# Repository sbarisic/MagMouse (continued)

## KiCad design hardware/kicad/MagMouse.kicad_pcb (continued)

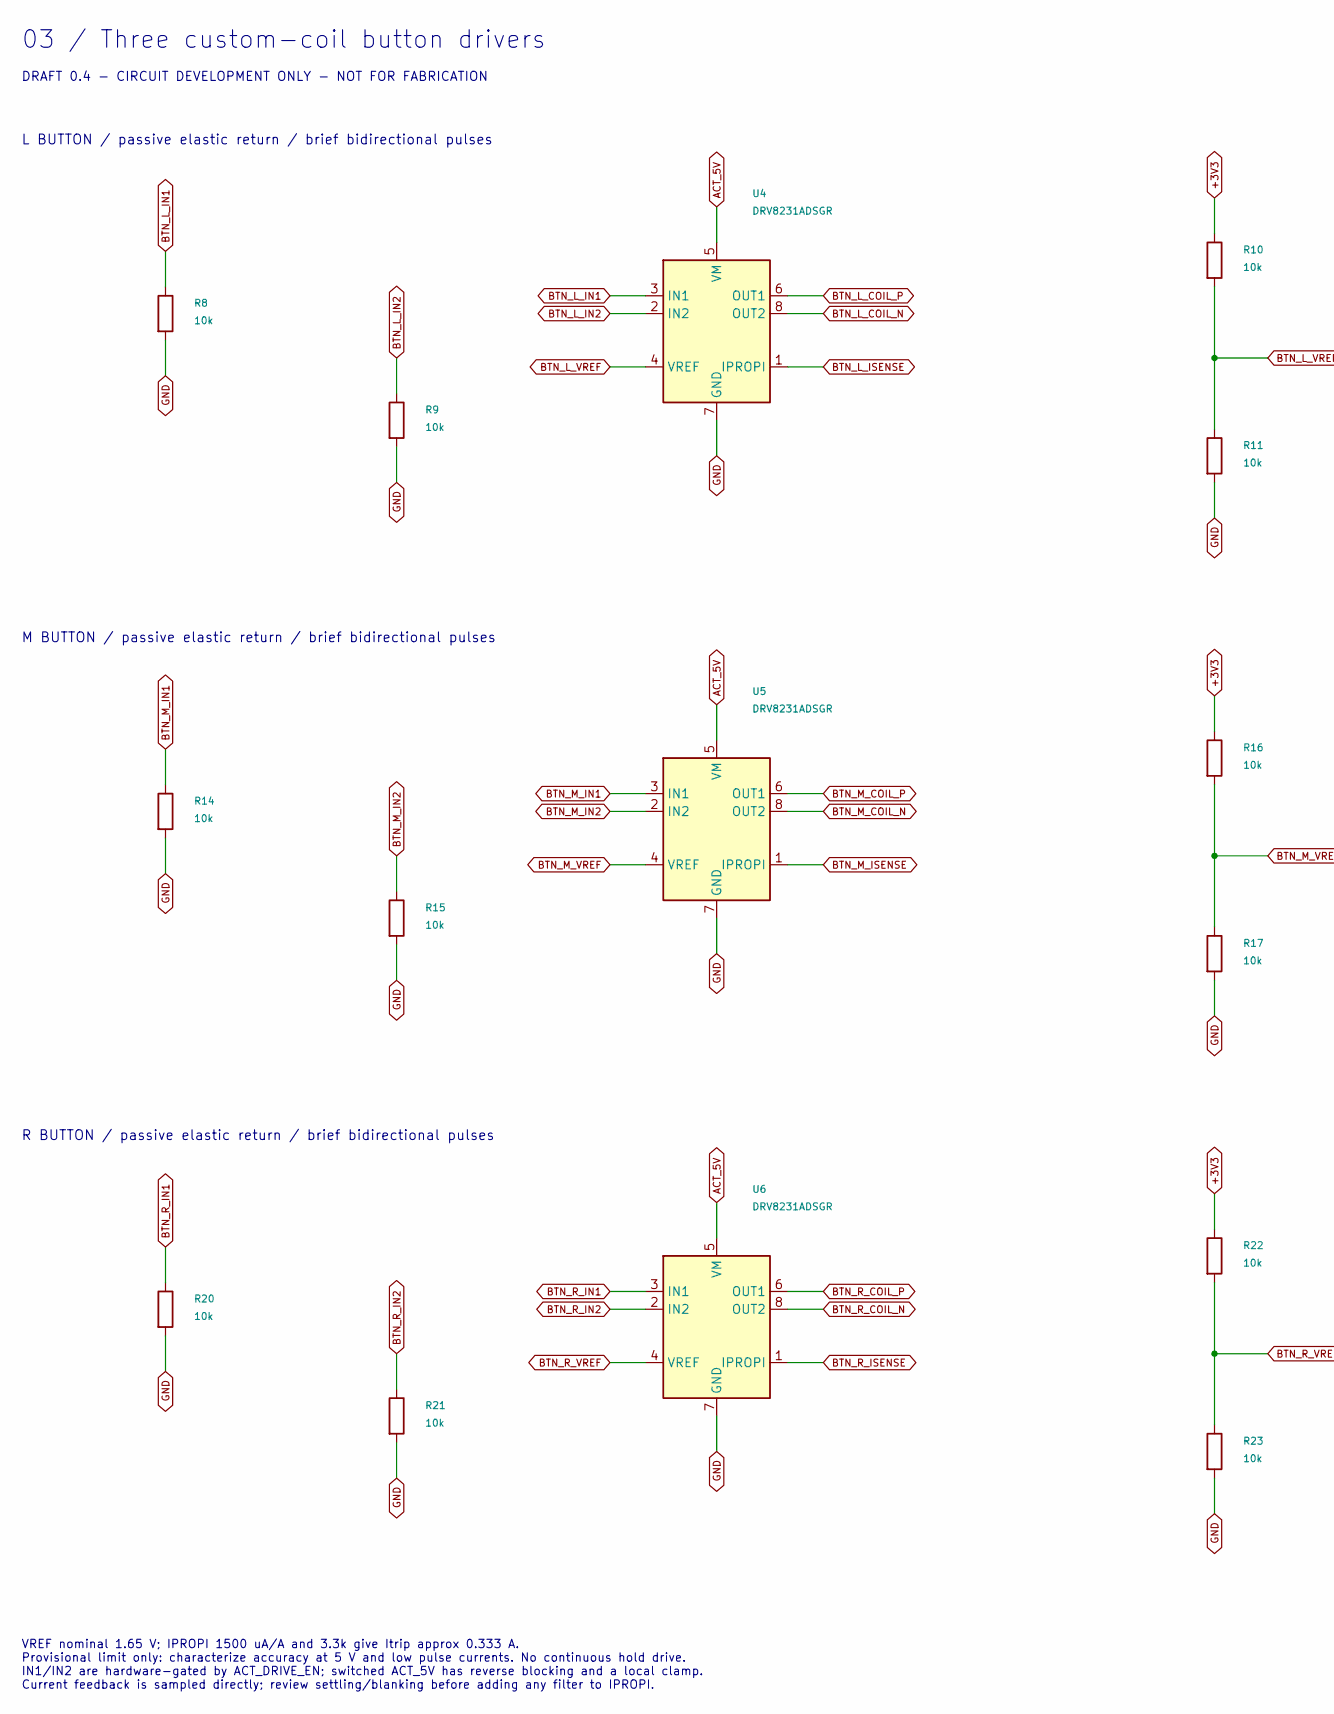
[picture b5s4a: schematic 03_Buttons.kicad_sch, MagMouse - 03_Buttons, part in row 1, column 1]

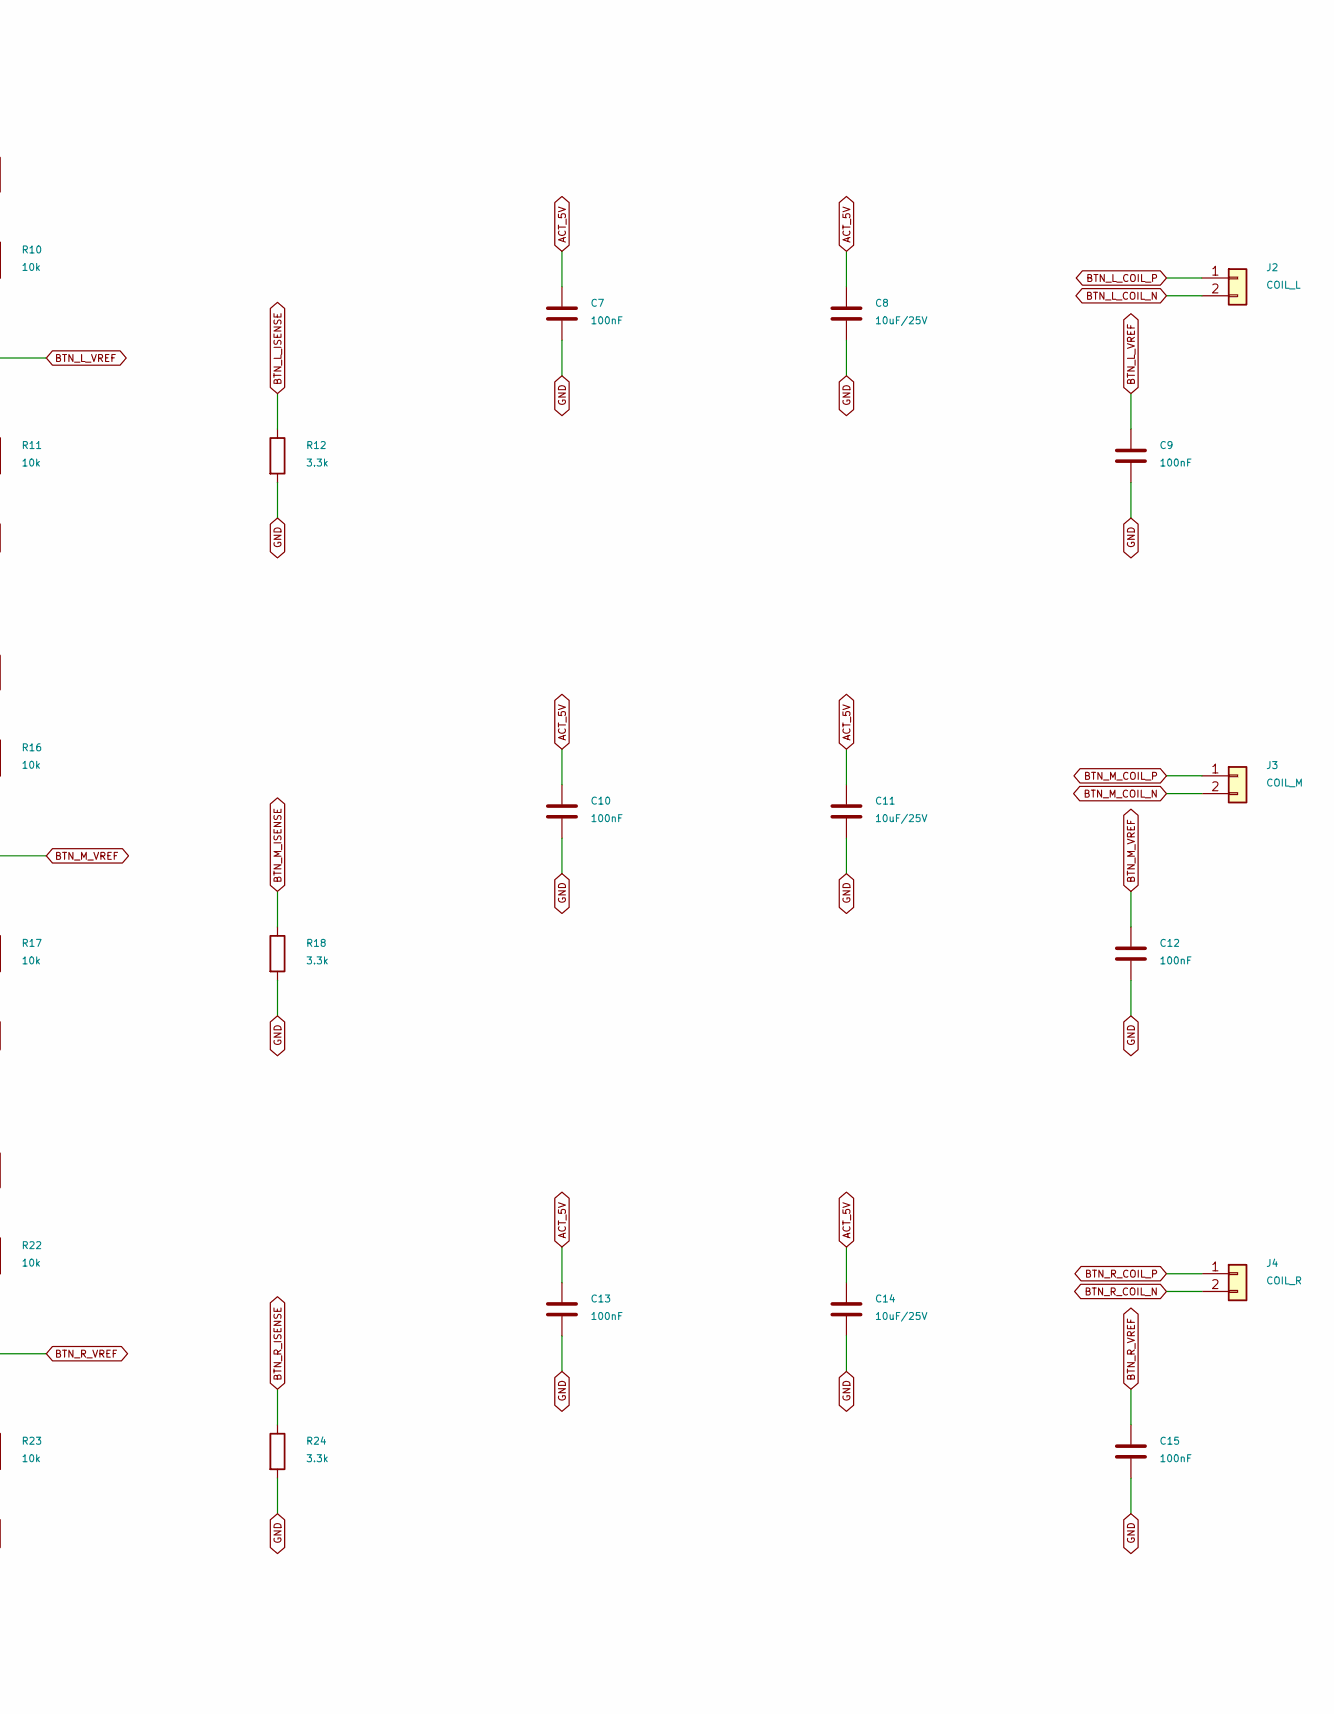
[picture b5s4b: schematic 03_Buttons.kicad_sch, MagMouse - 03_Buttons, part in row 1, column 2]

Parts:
C7, C9, C10, C12, C13, C15: 100nF; C_0603_1608Metric; MPN CC0603KRX7R9BB104; LCSC C14663
C8, C11, C14: 10uF/25V; C_0805_2012Metric; MPN CL21A106KAYNNNE; LCSC C15850
J2: COIL_L; JST_PH_B2B-PH-SM4-TB_1x02-1MP_P2.00mm_Vertical; MPN B2B-PH-SM4-TBT(LF)(SN); LCSC C265003
J3: COIL_M; JST_PH_B2B-PH-SM4-TB_1x02-1MP_P2.00mm_Vertical; MPN B2B-PH-SM4-TBT(LF)(SN); LCSC C265003
J4: COIL_R; JST_PH_B2B-PH-SM4-TB_1x02-1MP_P2.00mm_Vertical; MPN B2B-PH-SM4-TBT(LF)(SN); LCSC C265003
R8, R9, R10, R11, R14, R15, R16, R17, R20, R21, R22, R23: 10k; R_0603_1608Metric; MPN 0603WAF1002T5E; LCSC C25804
R12, R18, R24: 3.3k; R_0603_1608Metric; MPN 0603WAF3301T5E; LCSC C22978
U4, U5, U6: DRV8231ADSGR; Texas_DSG0008A_WSON-8-1EP_2x2mm_P0.5mm_EP0.9x1.6mm; MPN DRV8231ADSGR; LCSC C5139865

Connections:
+3V3: R10.1, R16.1, R22.1; also elsewhere on the board
ACT_5V: C7.1, C8.1, C10.1, C11.1, C13.1, C14.1, U4.5 (VM), U5.5 (VM), U6.5 (VM); also elsewhere on the board
BTN_L_COIL_N: J2.2, U4.8 (OUT2)
BTN_L_COIL_P: J2.1, U4.6 (OUT1)
BTN_L_IN1: R8.1, U4.3 (IN1); also elsewhere on the board
BTN_L_IN2: R9.1, U4.2 (IN2); also elsewhere on the board
BTN_L_ISENSE: R12.1, U4.1 (IPROPI); also elsewhere on the board
BTN_L_VREF: C9.1, R10.2, R11.1, U4.4 (VREF)
BTN_M_COIL_N: J3.2, U5.8 (OUT2)
BTN_M_COIL_P: J3.1, U5.6 (OUT1)
BTN_M_IN1: R14.1, U5.3 (IN1); also elsewhere on the board
BTN_M_IN2: R15.1, U5.2 (IN2); also elsewhere on the board
BTN_M_ISENSE: R18.1, U5.1 (IPROPI); also elsewhere on the board
BTN_M_VREF: C12.1, R16.2, R17.1, U5.4 (VREF)
BTN_R_COIL_N: J4.2, U6.8 (OUT2)
BTN_R_COIL_P: J4.1, U6.6 (OUT1)
BTN_R_IN1: R20.1, U6.3 (IN1); also elsewhere on the board
BTN_R_IN2: R21.1, U6.2 (IN2); also elsewhere on the board
BTN_R_ISENSE: R24.1, U6.1 (IPROPI); also elsewhere on the board
BTN_R_VREF: C15.1, R22.2, R23.1, U6.4 (VREF)
GND: C7.2, C8.2, C9.2, C10.2, C11.2, C12.2, C13.2, C14.2, C15.2, R8.2, R9.2, R11.2, R12.2, R14.2, R15.2, R17.2, R18.2, R20.2, R21.2, R23.2, R24.2, U4.7 (GND), U4.9 (GND), U5.7 (GND), U5.9 (GND), U6.7 (GND), U6.9 (GND); also elsewhere on the board

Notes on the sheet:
03 / Three custom-coil button drivers
DRAFT 0.4 - CIRCUIT DEVELOPMENT ONLY - NOT FOR FABRICATION
L BUTTON / passive elastic return / brief bidirectional pulses
M BUTTON / passive elastic return / brief bidirectional pulses
R BUTTON / passive elastic return / brief bidirectional pulses
VREF nominal 1.65 V; IPROPI 1500 uA/A and 3.3k give Itrip approx 0.333 A. Provisional limit only: characterize accuracy at 5 V and low pulse currents. No continuous hold drive. IN1/IN2 are hardware-gated by ACT_DRIVE_EN; switched ACT_5V has reverse blocking and a local clamp. Current feedback is sa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

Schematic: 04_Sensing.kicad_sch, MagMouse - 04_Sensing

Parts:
C16, C17, C18: 100nF; C_0603_1608Metric; MPN CC0603KRX7R9BB104; LCSC C14663
C19, C20, C21: 1uF/50V; C_0603_1608Metric; MPN CL10A105KB8NNNC; LCSC C15849
U7, U8, U9: TMAG5253BA2IQDMRR; Texas_X2SON-4-1EP_1.1x1.4mm_P0.5mm_EP0.8x0.6mm; MPN TMAG5253BA2IQDMRR; LCSC C35414983
U10: ADS7038IRTER; WQFN-16-1EP_3x3mm_P0.5mm_EP1.68x1.68mm; MPN ADS7038IRTER; LCSC C2871580

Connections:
+3V3: C16.1, C17.1, C18.1, C19.1, C20.1, U7.1 (VCC), U8.1 (VCC), U9.1 (VCC), U10.7 (AVDD), U10.10 (DVDD); also elsewhere on the board
ACT_VMON: U10.6 (AIN7); also elsewhere on the board
ADC_CS: U10.11 (~CS); also elsewhere on the board
ADC_DECAP: C21.1, U10.8 (DECAP)
BTN_L_ISENSE: U10.2 (AIN3); also elsewhere on the board
BTN_M_ISENSE: U10.3 (AIN4); also elsewhere on the board
BTN_R_ISENSE: U10.4 (AIN5); also elsewhere on the board
GND: C16.2, C17.2, C18.2, C19.2, C20.2, C21.2, U7.2 (GND), U7.5 (EP), U8.2 (GND), U8.5 (EP), U9.2 (GND), U9.5 (EP), U10.9 (GND), U10.17 (EP); also elsewhere on the board
HALL_EN: U7.3 (EN), U8.3 (EN), U9.3 (EN); also elsewhere on the board
HALL_L: U7.4 (OUT), U10.15 (AIN0)
HALL_M: U8.4 (OUT), U10.16 (AIN1)
HALL_R: U9.4 (OUT), U10.1 (AIN2)
SPI_MISO: U10.12 (SDO); also elsewhere on the board
SPI_MOSI: U10.14 (SDI); also elsewhere on the board
SPI_SCLK: U10.13 (SCLK); also elsewhere on the board
USB_IMON_ADC: U10.5 (AIN6); also elsewhere on the board

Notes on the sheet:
04 / Hall position and current acquisition
DRAFT 0.4 - CIRCUIT DEVELOPMENT ONLY - NOT FOR FABRICATION
AIN0-2: Hall position. AIN3-5: button current. AIN6: input current. AIN7: actuator rail voltage. Wheel phase-current acquisition needs a separate path; no ADC inputs remain free. Hall sensors share the ADC supply/reference. Validate acquisition settling and magnetic interference. Power telemetry ca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

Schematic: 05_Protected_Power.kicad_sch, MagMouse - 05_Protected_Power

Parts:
C24, C89: 1uF/50V; C_0603_1608Metric; MPN CL10A105KB8NNNC; LCSC C15849
C25, C26: 10nF; C_0603_1608Metric; MPN 0603B103K500NT; LCSC C57112
C88: 10uF/25V; C_0805_2012Metric; MPN CL21A106KAYNNNE; LCSC C15850
D3: BAT54-7-F; SOT-23; MPN BAT54-7-F; LCSC C106920
R29, R41: 22.1k; R_0603_1608Metric; MPN 0603WAF2212T5E; LCSC C25961
R30: 10k; R_0603_1608Metric; MPN 0603WAF1002T5E; LCSC C25804
R31, R32, R33, R34, R35, R36, R37, R38, R39, R40: 100k; R_0603_1608Metric; MPN 0603WAF1003T5E; LCSC C25803
R42, R43: 3.3k; R_0603_1608Metric; MPN 0603WAF3301T5E; LCSC C22978
R44, R45: 1k; R_0603_1608Metric; MPN 0603WAF1001T5E; LCSC C21190
U12, U13: TPS259470LRPWR; Texas_RPW0010A; MPN TPS259470LRPWR; LCSC C3662793

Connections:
ACT_5V: U13.6 (OUT); also elsewhere on the board
ACT_DRIVE_EN: D3.3 (K); also elsewhere on the board
ACT_DVDT: C26.1, U13.7 (DVDT)
ACT_FAULT_N: R45.1, U13.4 (FLT_N)
ACT_ILM: R42.1, R43.1, U13.9 (ILM)
ACT_OVLO: R40.2, R41.1, U13.2 (OVLO)
ACT_UVLO: D3.1 (A), R38.2, R39.1, U13.1 (EN_UVLO)
ACT_UV_1: R36.2, R37.1
ACT_UV_2: R37.2, R38.1
GND: C24.2, C25.2, C26.2, C88.2, C89.2, R30.2, R35.2, R39.2, R41.2, R42.2, R43.2, U12.8 (GND), U13.8 (GND); also elsewhere on the board
MCU_EN: R44.2, R45.2; also elsewhere on the board
PWR_5V: C88.1, C89.1, R36.1, R40.1, U12.6 (OUT), U13.5 (IN); also elsewhere on the board
USB_DVDT: C25.1, U12.7 (DVDT)
USB_FAULT_N: R44.1, U12.4 (FLT_N)
USB_ILM: U12.9 (ILM); also elsewhere on the board
USB_OVLO: R34.2, R35.1, U12.2 (OVLO)
USB_OV_1: R31.2, R32.1
USB_OV_2: R32.2, R33.1
USB_OV_3: R33.2, R34.1
USB_UVLO: R29.2, R30.1, U12.1 (EN_UVLO)
VBUS_USB: C24.1, R29.1, R31.1, U12.5 (IN); also elsewhere on the board

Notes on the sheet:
05 / Protected input and separately switched actuator rail
DRAFT 0.4 - CIRCUIT DEVELOPMENT ONLY - NOT FOR FABRICATION
U12: input OVLO/UVLO, soft-start, current limit and reverse blocking. ITIMER=NC: fastest response. U13: separate reverse blocking prevents actuator regeneration from reaching logic or USB. 2.02 A nominal branch limit. Faults hold MCU reset through 1k resistors. Source budgets and firmware state lim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
C88: local U12 output bypass. C1 remains beside the buck; do not rely on the long feed as local decoupling.
C89: local U13 input bypass. Place existing C40 at U13 OUT; C37-C39 remain rail storage.

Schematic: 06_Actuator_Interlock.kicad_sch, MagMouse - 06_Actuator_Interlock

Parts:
C27: 1uF/50V; C_0603_1608Metric; MPN CL10A105KB8NNNC; LCSC C15849
C28, C29, C30, C31: 100nF; C_0603_1608Metric; MPN CC0603KRX7R9BB104; LCSC C14663
R46, R47, R48, R49, R50, R51, R52, R53, R54, R55, R70: 10k; R_0603_1608Metric; MPN 0603WAF1002T5E; LCSC C25804
U15: SN74LVC1G123DCUR; VSSOP-8_2.3x2mm_P0.5mm; MPN SN74LVC1G123DCUR; LCSC C352969
U16, U17, U18: SN74LVC08APWR; TSSOP-14_4.4x5mm_P0.65mm; MPN SN74LVC08APWR; LCSC C465737

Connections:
+3V3: C28.1, C29.1, C30.1, C31.1, R46.1, U15.8 (VCC), U16.14 (VCC), U17.14 (VCC), U18.14 (VCC); also elsewhere on the board
ACT_DRIVE_EN: R49.1, U16.11 (4Y), U17.2 (1B), U17.5 (2B), U17.10 (3B), U17.13 (4B), U18.2 (1B), U18.5 (2B); also elsewhere on the board
ACT_HEARTBEAT: R47.1, U15.2 (B); also elsewhere on the board
ACT_PERMIT: U15.5 (Q), U16.12 (4A)
ACT_REQ: R48.1, U16.2 (1B); also elsewhere on the board
ARM_SOURCE: U16.3 (1Y), U16.4 (2A)
ARM_VALID: U15.3 (CLR_N), U16.6 (2Y), U16.13 (4B)
BTN_L_CMD1: R50.1, U17.1 (1A); also elsewhere on the board
BTN_L_CMD2: R51.1, U17.4 (2A); also elsewhere on the board
BTN_L_IN1: U17.3 (1Y); also elsewhere on the board
BTN_L_IN2: U17.6 (2Y); also elsewhere on the board
BTN_M_CMD1: R52.1, U17.9 (3A); also elsewhere on the board
BTN_M_CMD2: R53.1, U17.12 (4A); also elsewhere on the board
BTN_M_IN1: U17.8 (3Y); also elsewhere on the board
BTN_M_IN2: U17.11 (4Y); also elsewhere on the board
BTN_R_CMD1: R54.1, U18.1 (1A); also elsewhere on the board
BTN_R_CMD2: R55.1, U18.4 (2A); also elsewhere on the board
BTN_R_IN1: U18.3 (1Y); also elsewhere on the board
BTN_R_IN2: U18.6 (2Y); also elsewhere on the board
CC_OUT2_INV: U16.10 (3B); also elsewhere on the board
GND: C28.2, C29.2, C30.2, C31.2, R47.2, R48.2, R49.2, R50.2, R51.2, R52.2, R53.2, R54.2, R55.2, R70.2, U15.1 (A), U15.4 (GND), U16.7 (GND), U17.7 (GND), U18.7 (GND), U18.12 (4A), U18.13 (4B); also elsewhere on the board
HALL_EN: U16.5 (2B), U18.8 (3Y); also elsewhere on the board
MCU_EN: U18.10 (3B); also elsewhere on the board
SENS_REQ: R70.1, U18.9 (3A); also elsewhere on the board
SOURCE_3A: U16.8 (3Y); also elsewhere on the board
SOURCE_OK: U16.1 (1A), U16.9 (3A); also elsewhere on the board
WD_CEXT: C27.2, U15.6 (CEXT)
WD_RCEXT: C27.1, R46.2, U15.7 (RCEXT)

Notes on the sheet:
06 / Source-qualified arm, heartbeat timeout and drive gates
DRAFT 0.4 - CIRCUIT DEVELOPMENT ONLY - NOT FOR FABRICATION
~10 ms retriggerable heartbeat timeout. Arm requires 1.5/3 A source + ACT_REQ + HALL_EN. Permit gates every button IN and actuator power. Held-high heartbeat expires. Firmware: 1 ms refresh; keep all CMD low during rail ramp. See docs/power.md.

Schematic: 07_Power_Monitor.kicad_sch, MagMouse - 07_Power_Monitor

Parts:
C32, C33, C34, C35, C36: 100nF; C_0603_1608Metric; MPN CC0603KRX7R9BB104; LCSC C14663
D4: BAT54-7-F; SOT-23; MPN BAT54-7-F; LCSC C106920
Q1, Q2, Q3: 2N7002; SOT-23; MPN 2N7002; LCSC C8545
R56, R57, R60: 3.3k; R_0603_1608Metric; MPN 0603WAF3301T5E; LCSC C22978
R58: 33R; R_0603_1608Metric; MPN 0603WAF3300T5E; LCSC C23138
R59: 4.7k; R_0603_1608Metric; MPN 0603WAF4701T5E; LCSC C23162
R61: 10k; R_0603_1608Metric; MPN 0603WAF1002T5E; LCSC C25804
R62, R63, R66, R67, R71: 100k; R_0603_1608Metric; MPN 0603WAF1003T5E; LCSC C25803
R64: 1k; R_0603_1608Metric; MPN 0603WAF1001T5E; LCSC C21190
R65, R68: 22.1k; R_0603_1608Metric; MPN 0603WAF2212T5E; LCSC C25961
U14: SN74LVC2G04DCKR; SOT-363_SC-70-6; MPN SN74LVC2G04DCKR; LCSC C105251
U19: TLV9001IDBVR; SOT-23-5; MPN TLV9001IDBVR; LCSC C398363

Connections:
+3V3: C32.1, C34.1, D4.3 (K), R71.1, U14.5 (VCC), U19.5 (V+); also elsewhere on the board
ACT_5V: R67.1; also elsewhere on the board
ACT_VMON: C36.1, D4.1 (A), R67.2, R68.1; also elsewhere on the board
CC_OUT1: U14.1 (1A); also elsewhere on the board
CC_OUT2: U14.3 (2A); also elsewhere on the board
CC_OUT2_INV: U14.4 (2Y); also elsewhere on the board
GND: C32.2, C33.2, C34.2, C35.2, C36.2, Q1.2 (S), Q2.2 (S), Q3.2 (S), R58.2, R62.2, R63.2, R66.2, R68.2, U14.2 (GND), U19.2 (V-); also elsewhere on the board
ILM_BASE_1: R56.2, R57.1
ILM_BASE_2: R57.2, R58.1
ILM_HIGH_D: Q2.3 (D), R60.2, R61.2
ILM_MED_D: Q1.3 (D), R59.2
SOURCE_3A: Q2.1 (G), R63.1; also elsewhere on the board
SOURCE_OK: Q1.1 (G), R62.1, U14.6 (1Y); also elsewhere on the board
USB_ILM: R56.1, R59.1, R60.1, R61.1, U19.3 (IN+); also elsewhere on the board
USB_IMON_ADC: C33.1, R64.2; also elsewhere on the board
USB_IMON_BUF: R64.1, U19.1 (OUT), U19.4 (IN-)
VBUS_GATE: C35.1, Q3.1 (G), R65.2, R66.1
VBUS_PRESENT_N: Q3.3 (D), R71.2; also elsewhere on the board
VBUS_USB: R65.1; also elsewhere on the board

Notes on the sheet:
07 / Source-selected current limit and voltage/current telemetry
DRAFT 0.4 - CIRCUIT DEVELOPMENT ONLY - NOT FOR FABRICATION
CC OUT1/OUT2: HH detached, HL default, LH 1.5 A, LL 3 A. Missing detector supply leaves higher budgets OFF. ILIM = 3334 / R: 0.503 A / 1.212 A / 2.555 A nominal. This is fault protection; firmware enforces USB-state load budgets.
ADS7038 AIN6 = buffered input-current monitor; AIN7 = ACT rail voltage. GPIO1 = isolated, active-low VBUS presence (Q3). Voltage scale = 22.1 / 122.1. Current scale = 182 uA/A x effective ILM resistance; changes with CC state. Use raw CC status with each sample; discard mode-transition samples and 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

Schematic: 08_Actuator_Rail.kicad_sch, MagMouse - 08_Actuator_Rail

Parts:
C37, C38, C39, C40: 10uF/25V; C_0805_2012Metric; MPN CL21A106KAYNNNE; LCSC C15850
D1: SMBJ12A; D_SMB; MPN SMBJ12A; LCSC C151251
D2: SMBJ6.0A; D_SMB; MPN SMBJ6.0A; LCSC C83270
R69: 1k; R_0603_1608Metric; MPN 0603WAF1001T5E; LCSC C21190
TP1, TP10: VBUS_USB; TestPoint_Pad_D1.0mm
TP2, TP11: PWR_5V; TestPoint_Pad_D1.0mm
TP3, TP12: ACT_5V; TestPoint_Pad_D1.0mm
TP13: ACT_DRIVE_EN; TestPoint_Pad_D1.0mm
TP14: USB_ILM; TestPoint_Pad_D1.0mm
TP15: GND; TestPoint_Pad_D1.0mm

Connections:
ACT_5V: C37.1, C38.1, C39.1, C40.1, D2.1 (K), R69.1, TP3.1, TP12.1; also elsewhere on the board
ACT_DRIVE_EN: TP13.1; also elsewhere on the board
GND: C37.2, C38.2, C39.2, C40.2, D1.2 (A), D2.2 (A), R69.2, TP15.1; also elsewhere on the board
PWR_5V: TP2.1, TP11.1; also elsewhere on the board
USB_ILM: TP14.1; also elsewhere on the board
VBUS_USB: D1.1 (K), TP1.1, TP10.1; also elsewhere on the board

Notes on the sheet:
08 / Local actuator storage, clamp, discharge and review points
DRAFT 0.4 - CIRCUIT DEVELOPMENT ONLY - NOT FOR FABRICATION
ACT capacitance: 40 uF here + 30 uF at button drivers (nominal; DC bias/tolerance reduce storage). D2 SMBJ6.0A: 6 V standoff; 6.67-7.37 V breakdown; 10.3 V pulse clamp at datasheet test current. D1 SMBJ12A protects U12 input; U12 OVLO protects the downstream rails. U13 blocks actuator reverse power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

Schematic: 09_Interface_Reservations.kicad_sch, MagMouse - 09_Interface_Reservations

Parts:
R72, R73, R74, R75, R76, R77, R78, R79, R80: 10k; R_0603_1608Metric; MPN 0603WAF1002T5E; LCSC C25804
TP16: CS_PAW; TestPoint_Pad_D1.0mm
TP17: WHEEL_RUN_REQ; TestPoint_Pad_D1.0mm
TP18: CS_IMU; TestPoint_Pad_D1.0mm
TP19: OPT_CTRL; TestPoint_Pad_D1.0mm
TP20: MOTOR_SPI_MOSI; TestPoint_Pad_D1.0mm
TP21: MOTOR_SPI_SCLK; TestPoint_Pad_D1.0mm
TP22: MOTOR_SPI_MISO; TestPoint_Pad_D1.0mm
TP23: CS_ADC2; TestPoint_Pad_D1.0mm
TP24: CS_MA735; TestPoint_Pad_D1.0mm
TP25: CS_DRV8316; TestPoint_Pad_D1.0mm
TP26: PAW_MOTION_N; TestPoint_Pad_D1.0mm
TP27: IMU_INT1; TestPoint_Pad_D1.0mm
TP28: DRV_FAULT_N; TestPoint_Pad_D1.0mm
TP29: WHEEL_PWM_A; TestPoint_Pad_D1.0mm
TP30: RGB_DATA; TestPoint_Pad_D1.0mm
TP31: BOOT_SAFE_SPARE; TestPoint_Pad_D1.0mm
TP32: WHEEL_PWM_B; TestPoint_Pad_D1.0mm
TP33: WHEEL_PWM_C; TestPoint_Pad_D1.0mm

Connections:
+3V3: R72.1, R73.1, R74.1, R75.1, R76.1; also elsewhere on the board
BOOT_SAFE_SPARE: R80.1, TP31.1; also elsewhere on the board
CS_ADC2: R74.2, TP23.1; also elsewhere on the board
CS_DRV8316: R76.2, TP25.1; also elsewhere on the board
CS_IMU: R73.2, TP18.1; also elsewhere on the board
CS_MA735: R75.2, TP24.1; also elsewhere on the board
CS_PAW: R72.2, TP16.1; also elsewhere on the board
DRV_FAULT_N: TP28.1; also elsewhere on the board
GND: R77.2, R78.2, R79.2, R80.2; also elsewhere on the board
IMU_INT1: TP27.1; also elsewhere on the board
MOTOR_SPI_MISO: TP22.1; also elsewhere on the board
MOTOR_SPI_MOSI: TP20.1; also elsewhere on the board
MOTOR_SPI_SCLK: TP21.1; also elsewhere on the board
OPT_CTRL: R79.1, TP19.1; also elsewhere on the board
PAW_MOTION_N: TP26.1; also elsewhere on the board
RGB_DATA: R78.1, TP30.1; also elsewhere on the board
WHEEL_PWM_A: TP29.1; also elsewhere on the board
WHEEL_PWM_B: TP32.1; also elsewhere on the board
WHEEL_PWM_C: TP33.1; also elsewhere on the board
WHEEL_RUN_REQ: R77.1, TP17.1; also elsewhere on the board

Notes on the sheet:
09 / Allocated interfaces and boot defaults
DRAFT 0.4 - CIRCUIT DEVELOPMENT ONLY - NOT FOR FABRICATION
MCU connections and test pads retain the approved GPIO map. Sheets 10-13 implement wheel drive, ADC2, encoder, SPI isolation and autonomous braking. Optical, IMU and RGB remain open.
Only the N8 module is covered. Wheel voltage-domain isolation and hardware-qualified RUN are on sheets 10-12. Optical/IMU/RGB circuits must still respect their voltage and power-off requirements. GPIO46 stays LOW for download recovery. GPIO45 RGB interface must not pull the strap high during reset.

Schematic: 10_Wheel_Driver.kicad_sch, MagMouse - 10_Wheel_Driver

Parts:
C41, C42, C43, C49, C51: 100nF; C_0603_1608Metric; MPN CC0603KRX7R9BB104; LCSC C14663
C44, C45: 10uF/25V; C_0805_2012Metric; MPN CL21A106KAYNNNE; LCSC C15850
C46, C48: 1uF/50V; C_0603_1608Metric; MPN CL10A105KB8NNNC; LCSC C15849
C47: 47nF/50V; C_0603_1608Metric; MPN CL10B473KB8NNNC; LCSC C1622
C50: 22uF/25V; C_0805_2012Metric; MPN CL21A226MAQNNNE; LCSC C45783
J5: GB1806 phase wires; MotorWire_3x1mm_P2.54mm
Q4: 2N7002; SOT-23; MPN 2N7002; LCSC C8545
R81: 22R; R_0603_1608Metric; MPN 0603WAF220JT5E; LCSC C23345
R82: 10k; R_0603_1608Metric; MPN 0603WAF1002T5E; LCSC C25804
R83, R84, R90, R91, R92: 100k; R_0603_1608Metric; MPN 0603WAF1003T5E; LCSC C25803
U21: DRV8316RRGFR; Texas_RGF0040E; MPN DRV8316RRGFR; LCSC C5218861
U22: SN74LVC08APWR; TSSOP-14_4.4x5mm_P0.65mm; MPN SN74LVC08APWR; LCSC C465737

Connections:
+3V3: C51.1, U22.14 (VCC); also elsewhere on the board
ACT_5V: C41.1, C42.1, C43.1, C44.1, C45.1, C46.2, U21.9 (VM_1), U21.10 (VM_2), U21.11 (VM_3); also elsewhere on the board
ACT_DRIVE_EN: R84.1, U21.23 (nSLEEP), U22.1 (1A); also elsewhere on the board
DRV_AVDD: C48.1, C49.1, R82.1, U21.25 (AVDD), U21.37 (VREF); also elsewhere on the board
DRV_CS_LOCAL: U21.36 (nSCS); also elsewhere on the board
DRV_FAULT_LOCAL_N: U21.22 (nFAULT); also elsewhere on the board
DRV_INHA: R90.1, U21.27 (INHA), U22.6 (2Y)
DRV_INHB: R91.1, U21.29 (INHB), U22.8 (3Y)
DRV_INHC: R92.1, U21.31 (INHC), U22.11 (4Y)
DRV_MISO_LOCAL: U21.33 (SDO); also elsewhere on the board
DRV_MOSI_LOCAL: U21.34 (SDI); also elsewhere on the board
DRV_SCLK_LOCAL: U21.35 (SCLK); also elsewhere on the board
GND: C41.2, C42.2, C43.2, C44.2, C45.2, C48.2, C49.2, C50.2, C51.2, Q4.2 (S), R83.2, R84.2, R90.2, R91.2, R92.2, U21.2 (AGND_1), U21.4 (GND_BK), U21.12 (PGND_1), U21.15 (PGND_2), U21.18 (PGND_3), U21.26 (AGND_2), U21.41 (EP), U22.7 (GND); also elsewhere on the board
WHEEL_BUCK_OUT: C50.1, R81.2, U21.3 (FB_BK)
WHEEL_BUCK_SW: R81.1, U21.5 (SW_BK)
WHEEL_CP: C46.1, U21.8 (CP)
WHEEL_CPH: C47.1, U21.7 (CPH)
WHEEL_CPL: C47.2, U21.6 (CPL)
WHEEL_DRVOFF: Q4.3 (D), R82.2, U21.21 (DRVOFF)
WHEEL_PHASE_A: J5.1, U21.13 (OUTA_1), U21.14 (OUTA_2)
WHEEL_PHASE_B: J5.2, U21.16 (OUTB_1), U21.17 (OUTB_2)
WHEEL_PHASE_C: J5.3, U21.19 (OUTC_1), U21.20 (OUTC_2)
WHEEL_PWM_A: U22.4 (2A); also elsewhere on the board
WHEEL_PWM_B: U22.9 (3A); also elsewhere on the board
WHEEL_PWM_C: U22.12 (4A); also elsewhere on the board
WHEEL_RUN_EN: Q4.1 (G), R83.1, U21.28 (INLA), U21.30 (INLB), U21.32 (INLC), U22.3 (1Y), U22.5 (2B), U22.10 (3B), U22.13 (4B)
WHEEL_RUN_REQ: U22.2 (1B); also elsewhere on the board
WHEEL_SOA: U21.40 (SOA); also elsewhere on the board
WHEEL_SOB: U21.39 (SOB); also elsewhere on the board
WHEEL_SOC: U21.38 (SOC); also elsewhere on the board

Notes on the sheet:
10 / Wheel power stage and hardware shutdown
DRAFT 0.5 - CIRCUIT DEVELOPMENT ONLY - NOT FOR FABRICATION
3-PWM requires PWM_MODE = 10b; read back before RUN. Reset default is 6-PWM. DRVOFF high = all outputs Hi-Z. Low PWM alone is not shutdown. ACT_DRIVE_EN wakes the driver; RUN stays low during SPI configuration.
GB1806 is external; winding, phase sequence and current limits need measurement. Configure BUCK_DIS = 1; the 22R + 22uF termination remains fitted. AVDD supplies ADC2 and forward SPI buffers; no connection to system +3V3.

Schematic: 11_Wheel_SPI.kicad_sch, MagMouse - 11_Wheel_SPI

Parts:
C52, C53, C54, C55: 100nF; C_0603_1608Metric; MPN CC0603KRX7R9BB104; LCSC C14663
R86, R88, R98, R99: 10k; R_0603_1608Metric; MPN 0603WAF1002T5E; LCSC C25804
R87: 4.7k; R_0603_1608Metric; MPN 0603WAF4701T5E; LCSC C23162
R89, R94, R95, R96, R97, R100, R101: 100k; R_0603_1608Metric; MPN 0603WAF1003T5E; LCSC C25803
U24, U25, U26, U29: SN74LVC125APWR; TSSOP-14_4.4x5mm_P0.65mm; MPN SN74LVC125APWR; LCSC C7813

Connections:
+3V3: C53.1, U25.14 (VCC); also elsewhere on the board
ADC2_CS_LOCAL: R98.2, U26.8 (3Y); also elsewhere on the board
ADC2_MISO_LOCAL: R100.1, U25.9 (3A); also elsewhere on the board
ADC2_MOSI_LOCAL: U26.6 (2Y); also elsewhere on the board
ADC2_SCLK_LOCAL: U26.3 (1Y); also elsewhere on the board
CS_ADC2: U25.10 (3OE_N), U26.9 (3A); also elsewhere on the board
CS_DRV8316: U24.9 (3A), U25.1 (1OE_N); also elsewhere on the board
CS_MA735: U25.4 (2OE_N), U29.9 (3A); also elsewhere on the board
DRV_AVDD: C52.1, C54.1, R86.1, R87.1, R88.1, R98.1, U24.13 (4OE_N), U24.14 (VCC), U26.13 (4OE_N), U26.14 (VCC); also elsewhere on the board
DRV_CS_LOCAL: R86.2, U24.8 (3Y); also elsewhere on the board
DRV_FAULT_LOCAL_N: R88.2, R89.1, U25.12 (4A); also elsewhere on the board
DRV_FAULT_N: U25.11 (4Y); also elsewhere on the board
DRV_MISO_LOCAL: R87.2, U25.2 (1A); also elsewhere on the board
DRV_MOSI_LOCAL: U24.6 (2Y); also elsewhere on the board
DRV_SCLK_LOCAL: U24.3 (1Y); also elsewhere on the board
ENC_3V3: C55.1, R99.1, U29.13 (4OE_N), U29.14 (VCC); also elsewhere on the board
ENC_CS_LOCAL: R99.2, U29.8 (3Y); also elsewhere on the board
ENC_MISO_LOCAL: R101.1, U25.5 (2A); also elsewhere on the board
ENC_MOSI_LOCAL: U29.6 (2Y); also elsewhere on the board
ENC_SCLK_LOCAL: U29.3 (1Y); also elsewhere on the board
GND: C52.2, C53.2, C54.2, C55.2, R89.2, R94.2, R95.2, R96.2, R97.2, R100.2, R101.2, U24.1 (1OE_N), U24.4 (2OE_N), U24.7 (GND), U24.10 (3OE_N), U24.12 (4A), U25.7 (GND), U25.13 (4OE_N), U26.1 (1OE_N), U26.4 (2OE_N), U26.7 (GND), U26.10 (3OE_N), U26.12 (4A), U29.1 (1OE_N), U29.4 (2OE_N), U29.7 (GND), U29.10 (3OE_N), U29.12 (4A); also elsewhere on the board
MOTOR_SPI_MISO: U25.8 (3Y); also elsewhere on the board
MOTOR_SPI_MOSI: R97.1, U26.5 (2A); also elsewhere on the board
MOTOR_SPI_SCLK: R96.1, U26.2 (1A); also elsewhere on the board
SPI_MISO: U25.3 (1Y), U25.6 (2Y); also elsewhere on the board
SPI_MOSI: R95.1, U24.5 (2A), U29.5 (2A); also elsewhere on the board
SPI_SCLK: R94.1, U24.2 (1A), U29.2 (1A); also elsewhere on the board

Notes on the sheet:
11 / Power-domain SPI isolation
DRAFT 0.5 - CIRCUIT DEVELOPMENT ONLY - NOT FOR FABRICATION
Forward buffers use destination supplies and Ioff protection. Return buffers use MCU +3V3 and per-device CS. No simultaneous SPI2 chip selects. ADC2 conversions/configuration restart after every ACT power/sleep cycle. Driver nFAULT pull-up is in the AVDD domain: do not pull it low from an unpowered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

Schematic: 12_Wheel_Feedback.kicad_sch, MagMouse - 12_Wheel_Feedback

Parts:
C56, C57, C58, C63: 1uF/50V; C_0603_1608Metric; MPN CL10A105KB8NNNC; LCSC C15849
C59, C60, C61: 22pF/50V; C_0603_1608Metric; MPN CL10C220JB8NNNC; LCSC C1653
C64: 100nF; C_0603_1608Metric; MPN CC0603KRX7R9BB104; LCSC C14663
J6: ENCODER_8P; JST_SH_SM08B-SRSS-TB_1x08-1MP_P1.00mm_Horizontal; MPN SM08B-SRSS-TB(LF)(SN); LCSC C160407
R102, R103, R104: 330R; R_0603_1608Metric; MPN 0603WAF3300T5E; LCSC C23138
R105, R106, R107, R108, R109, R125: 0R; R_0603_1608Metric; MPN 0603WAF0000T5E; LCSC C21189
R110: 100k; R_0603_1608Metric; MPN 0603WAF1003T5E; LCSC C25803
U23: ADS7038IRTER; WQFN-16-1EP_3x3mm_P0.5mm_EP1.68x1.68mm; MPN ADS7038IRTER; LCSC C2871580
U28: TPS22919DCKR; SOT-363_SC-70-6; MPN TPS22919DCKR; LCSC C2149796

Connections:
+3V3: C63.1, U28.1 (IN); also elsewhere on the board
ADC2_CS_LOCAL: U23.11 (~CS); also elsewhere on the board
ADC2_DECAP: C58.1, U23.8 (DECAP)
ADC2_MISO_LOCAL: U23.12 (SDO); also elsewhere on the board
ADC2_MOSI_LOCAL: U23.14 (SDI); also elsewhere on the board
ADC2_SCLK_LOCAL: U23.13 (SCLK); also elsewhere on the board
ADC2_SPARE3: R105.1, U23.2 (AIN3)
ADC2_SPARE4: R106.1, U23.3 (AIN4)
ADC2_SPARE5: R107.1, U23.4 (AIN5)
ADC2_SPARE6: R108.1, U23.5 (AIN6)
ADC2_SPARE7: R109.1, U23.6 (AIN7)
DRV_AVDD: C56.1, C57.1, U23.7 (AVDD), U23.10 (DVDD); also elsewhere on the board
ENC_3V3: C64.1, J6.1, R125.2, U28.6 (OUT); also elsewhere on the board
ENC_CS_LOCAL: J6.6; also elsewhere on the board
ENC_MISO_LOCAL: J6.8; also elsewhere on the board
ENC_MOSI_LOCAL: J6.5; also elsewhere on the board
ENC_QOD: R125.1, U28.5 (QOD)
ENC_SCLK_LOCAL: J6.3; also elsewhere on the board
GND: C56.2, C57.2, C58.2, C59.2, C60.2, C61.2, C63.2, C64.2, J6.2, J6.4, J6.7, R105.2, R106.2, R107.2, R108.2, R109.2, R110.2, U23.9 (GND), U23.17 (EP), U28.2 (GND); also elsewhere on the board
HALL_EN: R110.1, U28.3 (ON); also elsewhere on the board
WHEEL_I_A: C59.1, R102.2, U23.15 (AIN0)
WHEEL_I_B: C60.1, R103.2, U23.16 (AIN1)
WHEEL_I_C: C61.1, R104.2, U23.1 (AIN2)
WHEEL_SOA: R102.1; also elsewhere on the board
WHEEL_SOB: R103.1; also elsewhere on the board
WHEEL_SOC: R104.1; also elsewhere on the board

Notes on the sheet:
12 / Wheel current ADC and encoder-board interface
DRAFT 0.8 - CIRCUIT DEVELOPMENT ONLY - NOT FOR FABRICATION
ADC2 and CSA share DRV_AVDD: ratiometric reference; both analog/digital ADC supplies turn off with the driver. CH3-7 are grounded through removable 0R links; CH3 bus-current sensing is not populated.
U27/C62 moved to hardware/encoder/Encoder.kicad_sch. U28 still switches ENC_3V3 with HALL_EN and QOD discharge. U29/U25 retain power-off SPI isolation. No GPIO change. Use an eight-wire pin-to-pin harness; confirm cable continuity.
SOx = AVDD/2 +/- gain * I. Initial gain target 1.2 V/A; calibrate zero and gain. 330R/22pF: fc = 21.9MHz. Multiplexed samples are not simultaneous. Prove common low-side window, settling, launch jitter and angle age.
TO UPRIGHT ENCODER BOARD J6 pin N -> J7 pin N 1 ENC_3V3 2 GND 3 SCLK (buffered) 4 GND 5 MOSI (buffered) 6 CS (buffered) 7 GND 8 MISO (return)

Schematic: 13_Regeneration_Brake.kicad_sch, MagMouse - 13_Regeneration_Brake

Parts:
C65, C66: 100nF; C_0603_1608Metric; MPN CC0603KRX7R9BB104; LCSC C14663
C67: 22pF/50V; C_0603_1608Metric; MPN CL10C220JB8NNNC; LCSC C1653
C68, C69: 10uF/25V; C_0805_2012Metric; MPN CL21A106KAYNNNE; LCSC C15850
Q5: AO3400A; SOT-23; MPN AO3400A; LCSC C20917
R111: 10k; R_0603_1608Metric; MPN 0603WAF1002T5E; LCSC C25804
R112, R114, R120: 100k; R_0603_1608Metric; MPN 0603WAF1003T5E; LCSC C25803
R113: 34.8k; R_0603_1608Metric; MPN 0603WAF3482T5E; LCSC C23141
R115, R116, R117: 1M; R_0603_1608Metric; MPN 0603WAF1004T5E; LCSC C22935
R119: 100R; R_0603_1608Metric; MPN 0603WAF1000T5E; LCSC C22775
R121, R122, R123, R124: 47R/2W; R_2512_6332Metric; MPN RC2512JK-7W47RL; LCSC C136992
TP34: ACT_5V; TestPoint_Pad_D1.0mm
TP35: BRAKE_REF; TestPoint_Pad_D1.0mm
TP36: BRAKE_OUT; TestPoint_Pad_D1.0mm
TP37: GND; TestPoint_Pad_D1.0mm
U30: TLV1811DBVR; SOT-23-5; MPN TLV1811DBVR; LCSC C5373003
U31: LM4040AIM3-2.5/NOPB; SOT-23; MPN LM4040AIM3-2.5/NOPB; LCSC C139302

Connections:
ACT_5V: C65.1, C68.1, C69.1, R111.1, R112.1, R121.1, R122.1, R123.1, R124.1, TP34.1, U30.5 (V+); also elsewhere on the board
BRAKE_DIV_TOP: R112.2, R113.1
BRAKE_DRAIN: Q5.3 (D), R121.2, R122.2, R123.2, R124.2
BRAKE_FB_1: R115.2, R116.1
BRAKE_FB_2: R116.2, R117.1
BRAKE_GATE: Q5.1 (G), R119.2, R120.1
BRAKE_OUT: R115.1, R119.1, TP36.1, U30.1 (OUT)
BRAKE_REF: C66.1, R111.2, TP35.1, U30.4 (IN-), U31.1 (K)
BRAKE_SENSE: C67.1, R113.2, R114.1, R117.2, U30.3 (IN+)
GND: C65.2, C66.2, C67.2, C68.2, C69.2, Q5.2 (S), R114.2, R120.2, TP37.1, U30.2 (V-), U31.2 (A); also elsewhere on the board

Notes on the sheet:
13 / Autonomous ACT rail regeneration brake
DRAFT 0.5 - CIRCUIT DEVELOPMENT ONLY - NOT FOR FABRICATION
No MCU or +3V3 supply dependency. Comparator/reference/push-pull gate drive are supplied from ACT_5V. Nominal hysteresis near 5.98V ON / 5.72V OFF; see wheel checks for tolerance corners. Four parallel 47R/2W resistors = 11.75 ohms; about 3.1W ON at 6V. D2 remains the secondary transient clamp.
PROVISIONAL ENERGY ENVELOPE: characterize at <=0.5W average returned power with temperature monitoring. Resistor ratings are not enclosed-board thermal acceptance. Verify unpowered-MCU braking, startup and overshoot.

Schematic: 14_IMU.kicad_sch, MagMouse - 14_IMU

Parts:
C70: 100nF; C_0603_1608Metric; MPN CC0603KRX7R9BB104; LCSC C14663
C71: 2.2uF/10V; C_0603_1608Metric; MPN CL10B225KP8NNNC; LCSC C100082
C72: 10nF; C_0603_1608Metric; MPN CL10B103KB8NNNC; LCSC C1589
R126, R127: 10k; R_0603_1608Metric; MPN 0603WAF1002T5E; LCSC C25804
U32: ICM-42688-P; LGA-14_3x2.5mm_P0.5mm_LayoutBorder3x4y; MPN ICM-42688-P; LCSC C1850418

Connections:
+3V3: C70.1, C71.1, C72.1, R127.1, U32.5 (VDDIO), U32.8 (VDD); also elsewhere on the board
CS_IMU: U32.12 (AP_CS); also elsewhere on the board
GND: C70.2, C71.2, C72.2, R126.2, U32.6 (GND), U32.7 (RESV_GND); also elsewhere on the board
IMU_INT1: R127.2, U32.4 (INT1); also elsewhere on the board
IMU_PIN9: R126.1, U32.9 (INT2_FSYNC_CLKIN)
SPI_MISO: U32.1 (AP_SDO); also elsewhere on the board
SPI_MOSI: U32.14 (AP_SDI); also elsewhere on the board
SPI_SCLK: U32.13 (AP_SCLK); also elsewhere on the board

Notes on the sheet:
14 / Inertial sensing on shared SPI2
DRAFT 0.6 - CIRCUIT DEVELOPMENT ONLY - NOT FOR FABRICATION
C70/C71: place at VDD pin 8. C72: place at VDDIO pin 5. Both supplies remain on system +3V3. SPI2 mode 0, initial target 10MHz; CS setup/hold and MISO release guard >=100ns. R73 on sheet 09 holds CS high at boot. Internal clock; INT1 active-low open-drain with R127 pull-up. Pin 7 must be grounded. 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
Pin 9 has a 10k pulldown to avoid shorting a configurable output; select FSYNC input and leave FSYNC disabled. Wait >=1ms after valid power before register access; read WHO_AM_I=0x47 and configure interface/interrupts. Keep IMU in sleep for USB suspend. Prove shared-bus operation and vibration reje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

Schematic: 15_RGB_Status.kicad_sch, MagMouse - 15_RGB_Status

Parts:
C73, C74: 10uF/25V; C_0805_2012Metric; MPN CL21A106KAYNNNE; LCSC C15850
C75, C76: 100nF; C_0603_1608Metric; MPN CC0603KRX7R9BB104; LCSC C14663
D5: SK6805-EC15; OPSCO_SK6805_EC15; MPN SK6805-EC15; LCSC C2890035
R128: 330R; R_0603_1608Metric; MPN 0603WAF3300T5E; LCSC C23138
R129: 100k; R_0603_1608Metric; MPN 0603WAF1003T5E; LCSC C25803
R130: 10k; R_0603_1608Metric; MPN 0603WAF1002T5E; LCSC C25804
TP38: RGB_5V; TestPoint_Pad_D1.0mm
TP39: RGB_DIN; TestPoint_Pad_D1.0mm
U33: TPS7A2450DBVR; SOT-23-5; MPN TPS7A2450DBVR; LCSC C2864436
U34: SN74LV1T34DBVR; SOT-23-5; MPN SN74LV1T34DBVR; LCSC C100024

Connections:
GND: C73.2, C74.2, C75.2, C76.2, D5.4 (GND), R129.2, R130.2, U33.2 (GND), U34.3 (GND); also elsewhere on the board
HALL_EN: U33.3 (EN); also elsewhere on the board
PWR_5V: C73.1, U33.1 (IN); also elsewhere on the board
RGB_5V: C74.1, C75.1, C76.1, D5.2 (VDD), R130.1, TP38.1, U33.5 (OUT), U34.5 (VCC)
RGB_BUFFER_OUT: R128.1, U34.4 (Y)
RGB_DATA: U34.2 (A); also elsewhere on the board
RGB_DIN: D5.1 (DIN), R128.2, R129.1, TP39.1

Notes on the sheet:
15 / Single-data-pin status LED with switched protected supply
DRAFT 0.6 - CIRCUIT DEVELOPMENT ONLY - NOT FOR FABRICATION
U33 caps the LED rail near 5V; in dropout RGB_5V follows PWR_5V minus dropout. This is not a boost supply. HALL_EN low disables RGB with Hall/encoder sleep; R130 discharges local storage. ACT_5V is never used. U34 shifts 3.3V data to the LED rail. R78 on sheet 09 preserves GPIO45 boot-low; no LED-r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
Firmware: hold data low during rail transitions; send black before suspend, then lower HALL_EN. Target 800kbps GRB/MSB-first; A1 timing 0=0.30/0.95us, 1=0.90/0.35us, reset low >=300us. Qualify startup/dropout, discharge, bus current and RGB_DIN timing on hardware. LED supply must stay 3.7..5.5V.

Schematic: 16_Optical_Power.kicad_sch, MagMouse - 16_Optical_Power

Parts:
C77, C78: 10uF/25V; C_0805_2012Metric; MPN CL21A106KAYNNNE; LCSC C15850
C79: 1nF/50V; C_0603_1608Metric; MPN CL10B102KB8NNNC; LCSC C1588
C81, C82: 2.2uF/10V; C_0603_1608Metric; MPN CL10B225KP8NNNC; LCSC C100082
C83, C85: 100nF; C_0603_1608Metric; MPN CC0603KRX7R9BB104; LCSC C14663
C84: 4.7uF/10V; C_0603_1608Metric; MPN CL10A475KP8NNNC; LCSC C1705
R132: 39R; R_0603_1608Metric; MPN 0603WAF390JT5E; LCSC C23154
TP40: OPT_3V3; TestPoint_Pad_D1.0mm
TP41: OPT_1V9; TestPoint_Pad_D1.0mm
TP42: OPT_VDDPIX; TestPoint_Pad_D1.0mm
U36: TLV75519PDBVR; SOT-23-5; MPN TLV75519PDBVR; LCSC C2865381
U38: TPS22918DBVR; SOT-23-6; MPN TPS22918DBVR; LCSC C131941

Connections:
+3V3: C77.1, C78.1, U38.1 (VIN); also elsewhere on the board
GND: C77.2, C78.2, C79.2, C81.2, C82.2, C83.2, C84.2, C85.2, U36.2 (GND), U38.2 (GND); also elsewhere on the board
HALL_EN: U38.3 (ON); also elsewhere on the board
OPT_1V9: C82.1, C83.1, R132.1, TP41.1, U36.5 (OUT); also elsewhere on the board
OPT_3V3: C81.1, TP40.1, U36.1 (IN), U36.3 (EN), U38.6 (VOUT); also elsewhere on the board
OPT_LED_P: R132.2; also elsewhere on the board
OPT_RAMP_CT: C79.1, U38.4 (CT)
OPT_VDDPIX: C84.1, C85.1, TP42.1; also elsewhere on the board

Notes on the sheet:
16 / PMW3360 controlled-rise supply and local bypass
DRAFT 0.7 - CIRCUIT DEVELOPMENT ONLY - NOT FOR FABRICATION
C79=1nF: TI typical 10..90% rise 1.68ms at 3.3V (equation estimate 1.914ms); not a guaranteed limit. HALL_EN enables optics after USB configuration; clear SENS_REQ during suspend. QOD is intentionally NC. U36 derives 1.9V from local VDDIO. Verify BOTH rails rise in 0.15..20ms and become valid withi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
R132 is the 39-ohm reference LED feed; do not fit 5V here. OPT_CTRL on sheet 17 controls reset only. Qualify startup, brownout, hot replug, ripple and current before USB/power acceptance. See OPTICAL_DESIGN.md.
